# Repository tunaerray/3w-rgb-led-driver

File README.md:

# 3W RGB LED Driver

A custom-designed 3W RGB LED driver board with PWM dimming capability, developed for an Autonomous Underwater Vehicle (AUV).

## Overview

This board was designed to control the color output of a 3W RGB LED by adjusting each channel independently via PWM signals. The primary purpose is to support the AUV's image processing system by providing tunable, high-intensity underwater illumination.

## Features

- 3W RGB LED driving capability
- Independent PWM dimming for red, green, and blue channels
- Designed for underwater AUV integration
- Supports color-based object detection for computer vision tasks
- Tunable illumination for different underwater visibility conditions

## Use Case

Underwater visibility is limited, and colors can shift significantly with depth. By dynamically adjusting the RGB LED channels using PWM, the AUV's camera can capture more consistent color data.

This improves the reliability of image processing and object detection algorithms in underwater environments.

## Hardware

- **LED Type:** 3W RGB LED
- **Control Method:** Independent PWM dimming
- **Channels:** Red, green, and blue
- **Application:** Autonomous Underwater Vehicle lighting system
- **Purpose:** Image processing and object detection support

## Images

### PCB Front

### PCB Back

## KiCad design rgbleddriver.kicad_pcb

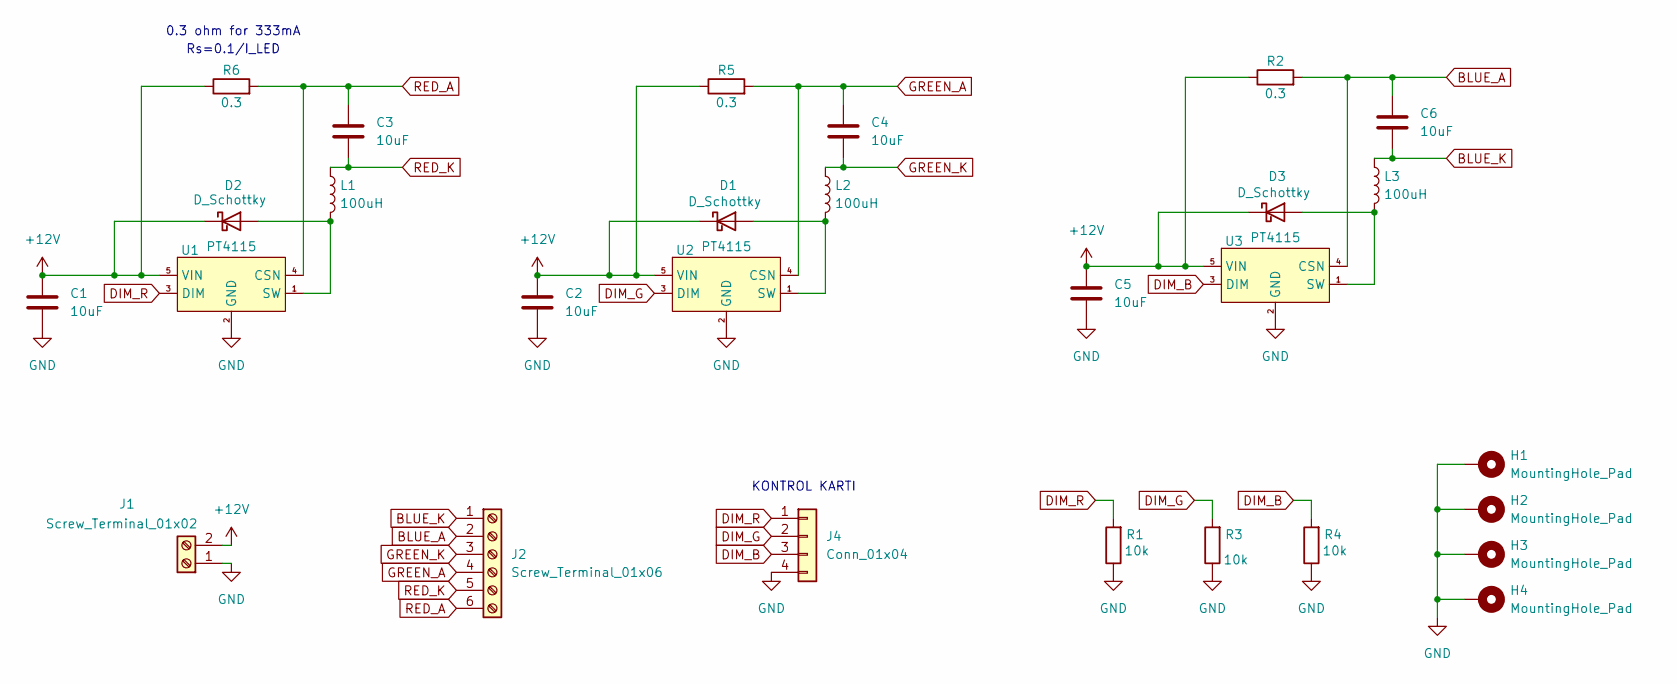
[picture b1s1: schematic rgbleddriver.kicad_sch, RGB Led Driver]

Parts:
C1, C2, C3, C4, C5, C6: 10uF; C_1210_3225Metric
D1, D2, D3: D_Schottky; D_SOD-123
H1, H2, H3, H4: MountingHole_Pad; MountingHole_4.3mm_M4_Pad_Via
J1: Screw_Terminal_01x02; TerminalBlock_Phoenix_PT-1,5-2-3.5-H_1x02_P3.50mm_Horizontal
J2: Screw_Terminal_01x06; TerminalBlock_Phoenix_PT-1,5-6-3.5-H_1x06_P3.50mm_Horizontal
J4: Conn_01x04; PinSocket_1x04_P2.54mm_Vertical
L1, L2, L3: 100uH; L_SOREDE_SNR.1050_10x10x5mm
R1, R3, R4: 10k; R_1206_3216Metric
R2, R5, R6: 0.3; R_1206_3216Metric
U1, U2, U3: PT4115; SOT-89-5

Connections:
+12V: C1.1, C2.1, C5.1, D1.1 (K), D2.1 (K), D3.1 (K), J1.2, R2.1, R5.1, R6.1, U1.5 (VIN), U2.5 (VIN), U3.5 (VIN)
BLUE_A: C6.1, J2.2, R2.2, U3.4 (CSN)
BLUE_K: C6.2, J2.1, L3.1
DIM_B: J4.3, R4.2, U3.3 (DIM)
DIM_G: J4.2, R3.2, U2.3 (DIM)
DIM_R: J4.1, R1.2, U1.3 (DIM)
GND: C1.2, C2.2, C5.2, H1.1, H2.1, H3.1, H4.1, J1.1, J4.4, R1.1, R3.1, R4.1, U1.2 (GND), U2.2 (GND), U3.2 (GND)
GREEN_A: C4.1, J2.4, R5.2, U2.4 (CSN)
GREEN_K: C4.2, J2.3, L2.1
unnamed: D1.2 (A), L2.2, U2.1 (SW)
unnamed: D2.2 (A), L1.2, U1.1 (SW)
unnamed: D3.2 (A), L3.2, U3.1 (SW)
RED_A: C3.1, J2.6, R6.2, U1.4 (CSN)
RED_K: C3.2, J2.5, L1.1

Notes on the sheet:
0.3 ohm for 333mA
KONTROL KARTI
Rs=0.1/I_LED

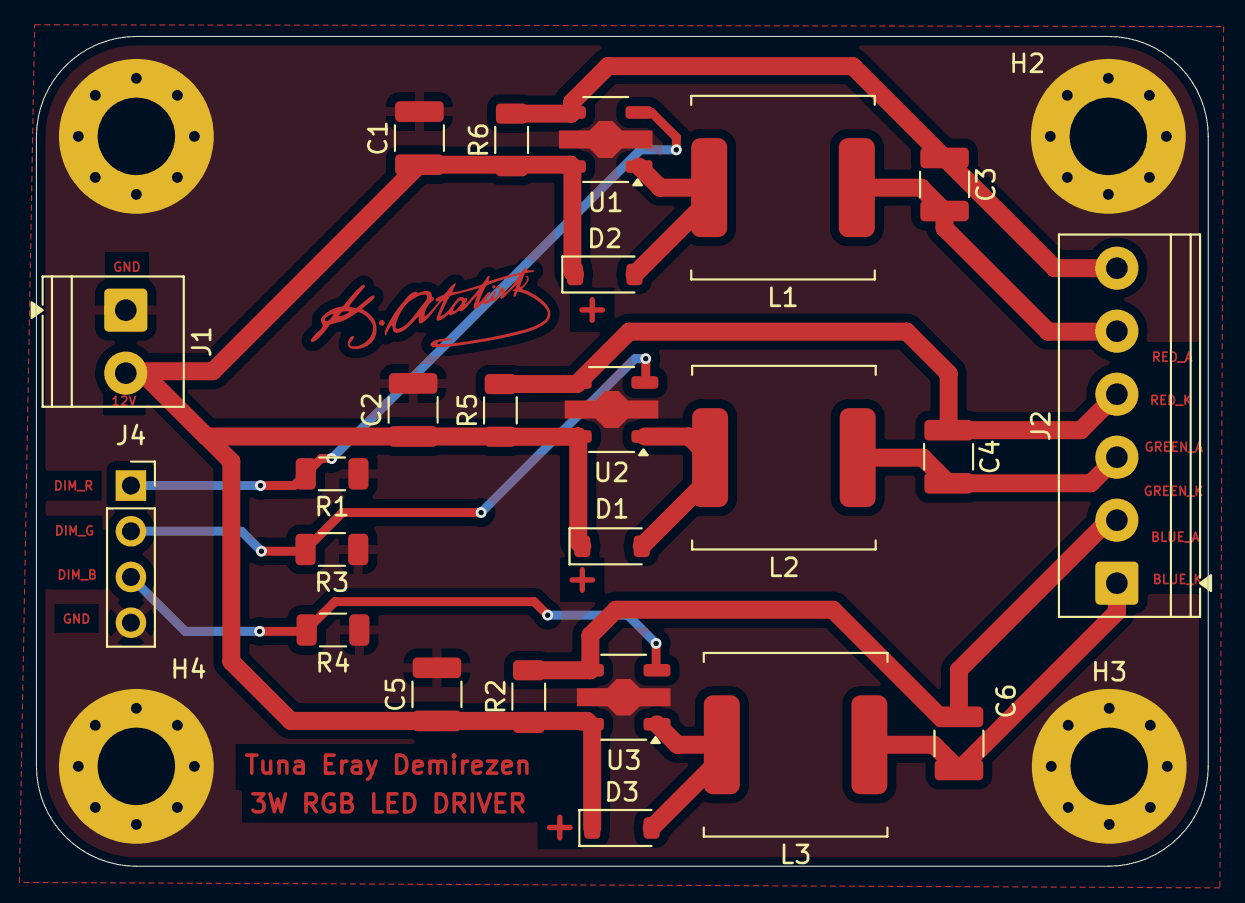
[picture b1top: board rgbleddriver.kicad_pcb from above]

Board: 2 copper layers, 65.1 x 46.1 mm, 28 parts (0 on the bottom side), 14 nets.

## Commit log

2026-05-30 Add KiCad PCB project files and BOM
2026-05-30 Add PCB images (front, back, layout)
2026-05-30 Add PCB images to README
2026-05-30 Add Gerber files for PCB manufacturing
2026-06-01 Revise README for improved clarity and detail
    Updated the README to enhance clarity and detail regarding the RGB LED driver board's features, use case, and hardware specifications.
2026-06-03 Update revised RGB LED driver PCB files
2026-06-03 Move images and gerber zip to repo root, remove subfolders
